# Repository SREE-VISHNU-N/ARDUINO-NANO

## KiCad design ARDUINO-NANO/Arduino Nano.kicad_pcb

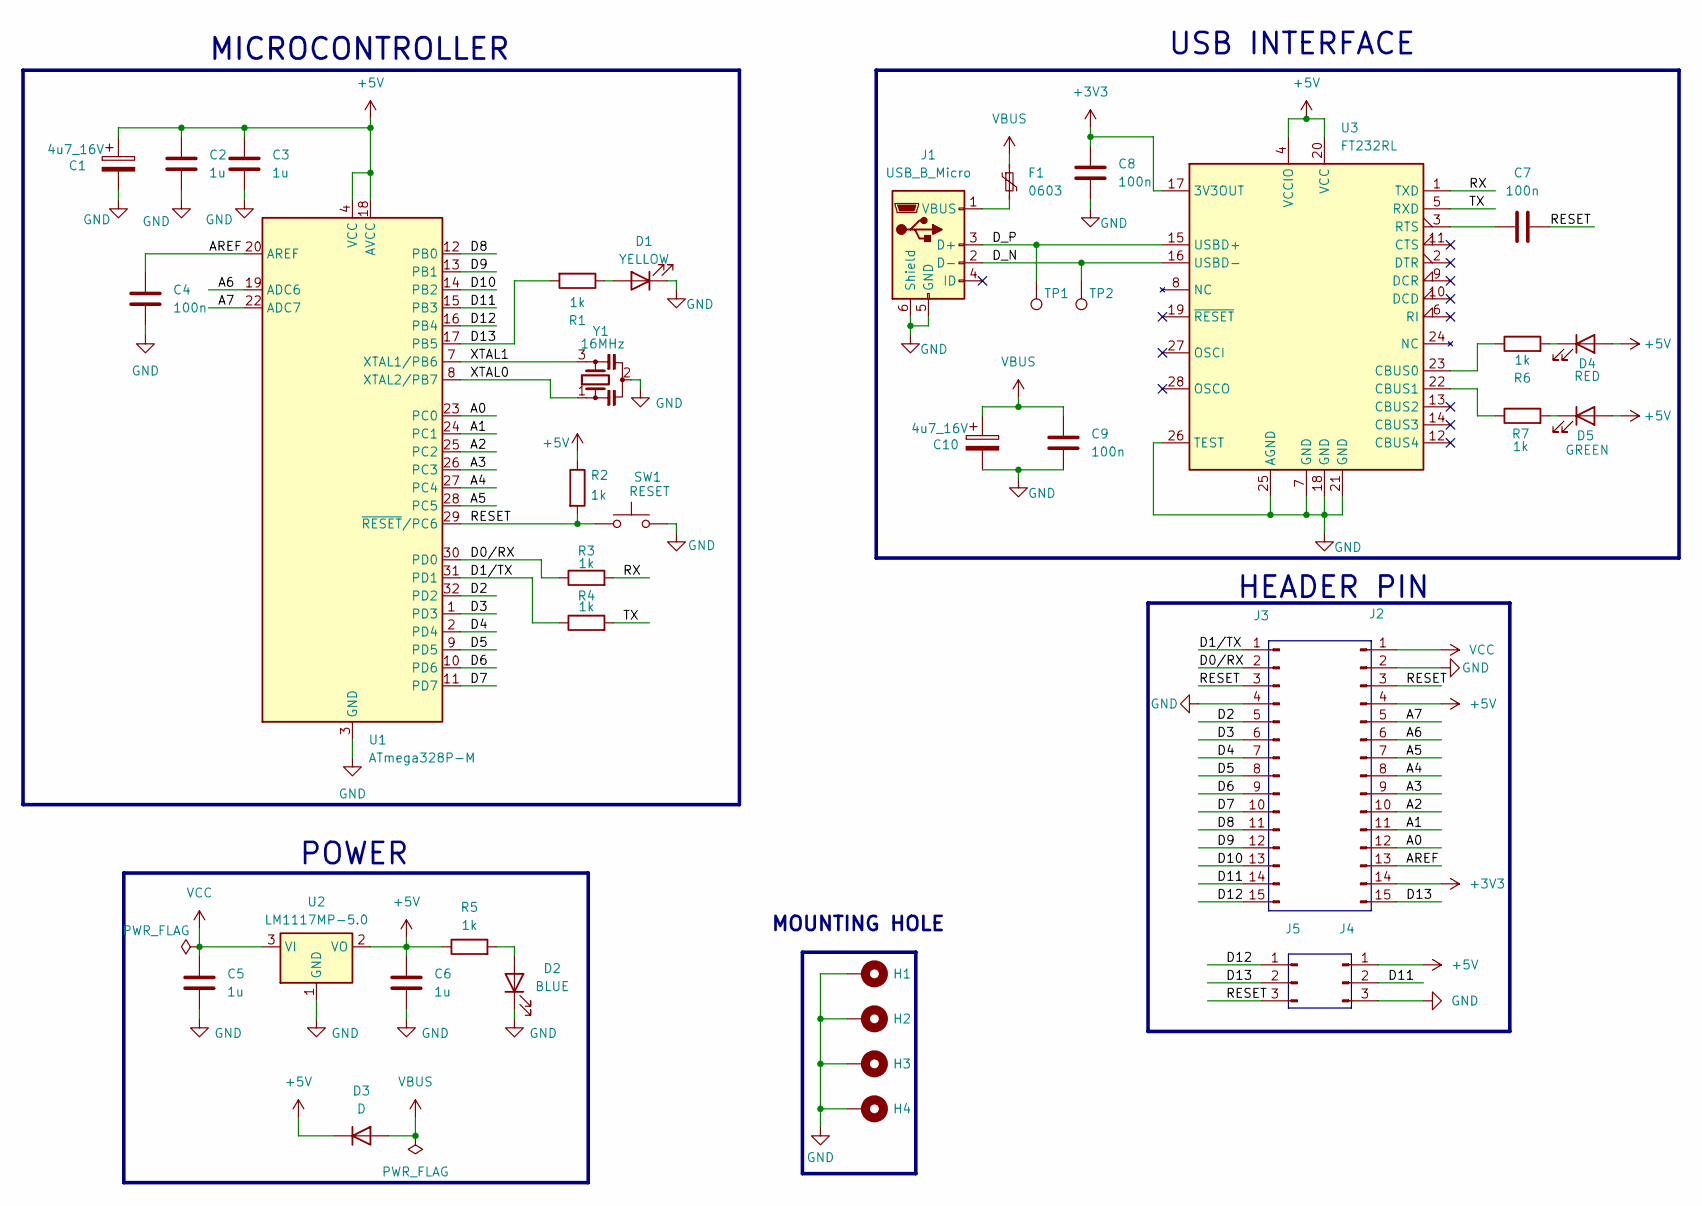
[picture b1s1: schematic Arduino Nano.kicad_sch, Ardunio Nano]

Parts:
C1, C10: 4u7_16V; CP_EIA-3216-10_Kemet-I
C2, C3, C5, C6: 1u; C_0603_1608Metric
C4, C7, C8, C9: 100n; C_0603_1608Metric
D1: YELLOW; LED_0805_2012Metric
D2: BLUE; LED_0805_2012Metric
D3: D; D_MicroSMP_AK
D4: RED; LED_0805_2012Metric
D5: GREEN; LED_0805_2012Metric
F1: 0603; D_0603_1608Metric
H1, H2, H3, H4: MountingHole_Pad; MountingHole_2.2mm_M2_DIN965_Pad
J1: USB_B_Micro; USB_Micro-B_Wuerth_629105150521
J2, J3: Conn_01x15_Pin; PinHeader_1x15_P2.00mm_Vertical
J4, J5: Conn_01x03_Pin; PinHeader_1x03_P1.27mm_Vertical
R1, R2, R3, R4, R5, R6, R7: 1k; R_0603_1608Metric
SW1: RESET; Panasonic_EVQPUK_EVQPUB
TP1, TP2: TestPoint; TestPoint_Pad_D1.0mm
U1: ATmega328P-M; QFN-32-1EP_5x5mm_P0.5mm_EP3.1x3.1mm
U2: LM1117MP-5.0; SOT-223-3_TabPin2
U3: FT232RL; SSOP-28_5.3x10.2mm_P0.65mm
Y1: 16MHz; Resonator_SMD_Murata_CSTxExxV-3Pin_3.0x1.1mm

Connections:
+3V3: C8.2, J2.14, U3.17 (3V3OUT)
+5V: C1.1, C2.1, C3.1, C6.1, D3.1 (K), D4.2 (A), D5.2 (A), J2.4, J4.1, R2.1, R5.1, U1.4 (VCC), U1.6 (VCC), U1.18 (AVCC), U2.2 (VO), U3.4 (VCCIO), U3.20 (VCC)
/A0: J2.12, U1.23 (PC0)
/A1: J2.11, U1.24 (PC1)
/A2: J2.10, U1.25 (PC2)
/A3: J2.9, U1.26 (PC3)
/A4: J2.8, U1.27 (PC4)
/A5: J2.7, U1.28 (PC5)
/A6: J2.6, U1.19 (ADC6)
/A7: J2.5, U1.22 (ADC7)
/AREF: C4.1, J2.13, U1.20 (AREF)
/D0/RX: J3.2, R3.1, U1.30 (PD0)
/D1/TX: J3.1, R4.1, U1.31 (PD1)
/D2: J3.5, U1.32 (PD2)
/D3: J3.6, U1.1 (PD3)
/D4: J3.7, U1.2 (PD4)
/D5: J3.8, U1.9 (PD5)
/D6: J3.9, U1.10 (PD6)
/D7: J3.10, U1.11 (PD7)
/D8: J3.11, U1.12 (PB0)
/D9: J3.12, U1.13 (PB1)
/D10: J3.13, U1.14 (PB2)
/D11: J3.14, J4.2, U1.15 (PB3)
/D12: J3.15, J5.1, U1.16 (PB4)
/D13: J2.15, J5.2, R1.2, U1.17 (PB5)
/D_N: J1.2 (D-), TP2.1, U3.16 (USBD-)
/D_P: J1.3 (D+), TP1.1, U3.15 (USBD+)
/RESET: C7.2, J2.3, J3.3, J5.3, R2.2, SW1.1, U1.29 (~RESET/PC6)
/RX: R3.2, U3.1 (TXD)
/TX: R4.2, U3.5 (RXD)
/XTAL0: U1.8 (XTAL2/PB7), Y1.1
/XTAL1: U1.7 (XTAL1/PB6), Y1.3
GND: C1.2, C2.2, C3.2, C4.2, C5.2, C6.2, C8.1, C9.1, C10.2, D1.1 (K), D2.1 (K), H1.1, H2.1, H3.1, H4.1, J1.5 (GND), J1.6 (Shield), J2.2, J3.4, J4.3, SW1.2, U1.3 (GND), U1.5 (GND), U1.21 (GND), U1.33 (GND), U2.1 (GND), U3.7 (GND), U3.18 (GND), U3.21 (GND), U3.25 (AGND), U3.26 (TEST), Y1.2
unnamed: D1.2 (A), R1.1
unnamed: D2.2 (A), R5.2
unnamed: D4.1 (K), R6.2
unnamed: D5.1 (K), R7.2
unnamed: F1.2, J1.1 (VBUS)
unnamed: R6.1, U3.23 (CBUS0)
unnamed: R7.1, U3.22 (CBUS1)
unnamed: C7.1, U3.3 (RTS)
VBUS: C9.2, C10.1, D3.2 (A), F1.1
VCC: C5.1, J2.1, U2.3 (VI)

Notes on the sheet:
USB INTERFACE
HEADER PIN
MICROCONTROLLER
POWER
MOUNTING HOLE

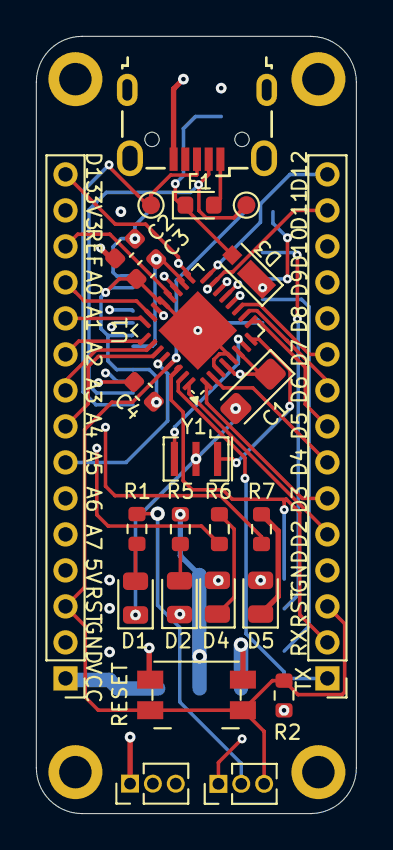
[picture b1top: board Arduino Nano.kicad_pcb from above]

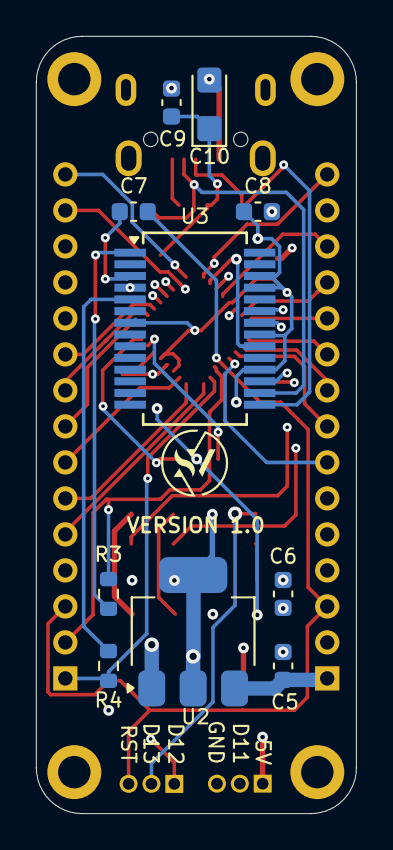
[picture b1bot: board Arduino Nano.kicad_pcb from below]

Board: 4 copper layers, 17.8 x 43.2 mm, 39 parts (10 on the bottom side), 43 nets.

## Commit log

2025-02-24 Create Arduino
2025-02-24 Create Footprint
2025-02-24 Create Gerber
2025-02-24 Create Bom
